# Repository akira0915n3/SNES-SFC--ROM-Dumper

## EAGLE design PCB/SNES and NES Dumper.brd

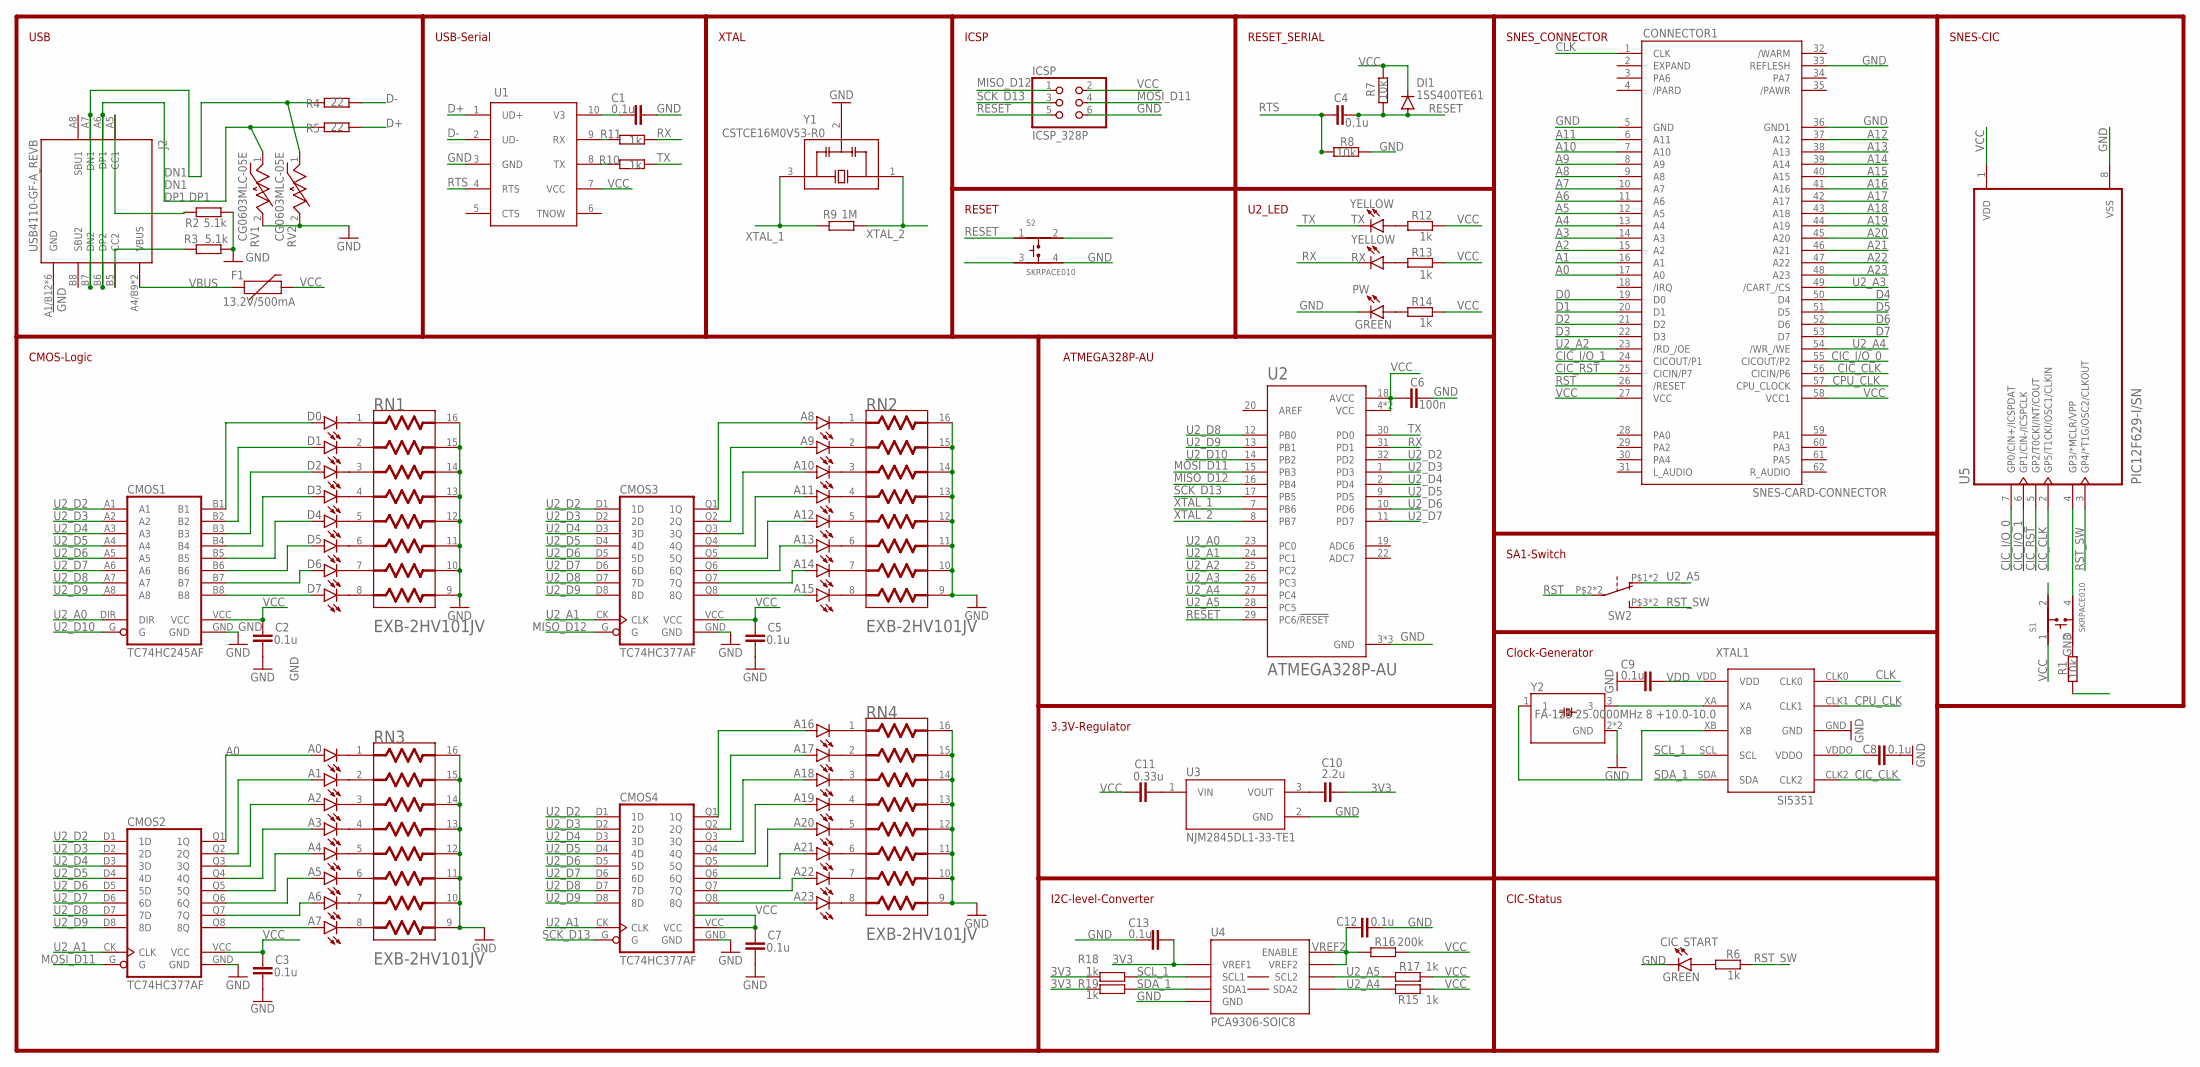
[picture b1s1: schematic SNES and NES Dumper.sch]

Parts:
A0, A1, A2, A3, A4, A5, A6, A7, A8, A9, A10, A11, A12, A13, A14, A15, A16, A17, A18, A19, A20, A21, A22, A23: YELLOW; SML0805
C1, C2, C3, C4, C5, C7, C8, C9, C12, C13: 0.1u; C0603
C6: 100n; C0603
C10: 2.2u; C0603
C11: 0.33u; C0603
CIC_START: GREEN; SML0805
CMOS1: TC74HC245AF; SO20W
CMOS2, CMOS3, CMOS4: TC74HC377AF; SO20W
CONNECTOR1: SNES-CARD-CONNECTOR; CON
D0, D1, D2, D3, D4, D5, D6, D7: YELLOW; SML0805
DI1: 1SS400TE61; SOD523
F1: 13.2V/500mA; 1206
ICSP: ICSP_328P; 2X03
J2: USB4110-GF-A_REVB; GCT_USB4110-GF-A_REVB
PW: GREEN; SML0805
R1, R7, R8: 10k; R0603
R2, R3: 5.1k; R0603
R4, R5: 22; R0603
R6, R10, R11, R12, R13, R14, R15, R17, R18, R19: 1k; R0603
R9: 1M; R0603
R16: 200k; R0603
RN1, RN2, RN3, RN4: PANASONIC_EXB-2HV101JVPANASONIC_EXB-2HV101JV_0_0; PANASONIC_EXB-2HV101JV_0
RV1, RV2: CG0603MLC-05E; VARC1608X56N
RX: YELLOW; SML0805
S1, S2: SKRPACE010; SW_SKRPACE010
SW2: ALPS_SSSS213202
TX: YELLOW; SML0805
U1: CH340E; MSOP10
U2: ATMEGA328P-AU; QFP80P900X900X120-32N
U3: NJM2845DL1-33-TE1; DPAK228P968X238-4N
U4: PCA9306-SOIC8; SOIC-8
U5: PIC12F629-I/SN; SOIC127P600X175-8N
XTAL1: SI5351; SI5351A-B-GTR
Y1: CSTCE16M0V53-R0; OSC_CSTCE16M0V53-R0
Y2: FA-128 25.0000MHz 8 +10.0-10.0; OSCSC320X250X100N

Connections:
3V3: C10.2, C13.2, R18.2, R19.2, U4.1 (VREF1)
A0: A0.A, CMOS2.Q1 (1Q), CONNECTOR1.17 (A0)
A1: A1.A, CMOS2.Q2 (2Q), CONNECTOR1.16 (A1)
A2: A2.A, CMOS2.Q3 (3Q), CONNECTOR1.15 (A2)
A3: A3.A, CMOS2.Q4 (4Q), CONNECTOR1.14 (A3)
A4: A4.A, CMOS2.Q5 (5Q), CONNECTOR1.13 (A4)
A5: A5.A, CMOS2.Q6 (6Q), CONNECTOR1.12 (A5)
A6: A6.A, CMOS2.Q7 (7Q), CONNECTOR1.11 (A6)
A7: A7.A, CMOS2.Q8 (8Q), CONNECTOR1.10 (A7)
A8: A8.A, CMOS3.Q1 (1Q), CONNECTOR1.9 (A8)
A9: A9.A, CMOS3.Q2 (2Q), CONNECTOR1.8 (A9)
A10: A10.A, CMOS3.Q3 (3Q), CONNECTOR1.7 (A10)
A11: A11.A, CMOS3.Q4 (4Q), CONNECTOR1.6 (A11)
A12: A12.A, CMOS3.Q5 (5Q), CONNECTOR1.37 (A12)
A13: A13.A, CMOS3.Q6 (6Q), CONNECTOR1.38 (A13)
A14: A14.A, CMOS3.Q7 (7Q), CONNECTOR1.39 (A14)
A15: A15.A, CMOS3.Q8 (8Q), CONNECTOR1.40 (A15)
A16: A16.A, CMOS4.Q1 (1Q), CONNECTOR1.41 (A16)
A17: A17.A, CMOS4.Q2 (2Q), CONNECTOR1.42 (A17)
A18: A18.A, CMOS4.Q3 (3Q), CONNECTOR1.43 (A18)
A19: A19.A, CMOS4.Q4 (4Q), CONNECTOR1.44 (A19)
A20: A20.A, CMOS4.Q5 (5Q), CONNECTOR1.45 (A20)
A21: A21.A, CMOS4.Q6 (6Q), CONNECTOR1.46 (A21)
A22: A22.A, CMOS4.Q7 (7Q), CONNECTOR1.47 (A22)
A23: A23.A, CMOS4.Q8 (8Q), CONNECTOR1.48 (A23)
CIC_CLK: CONNECTOR1.56 (CICIN/P6), U5.2 (GP5/T1CKI/OSC1/CLKIN), XTAL1.CLK2
CIC_I/O_0: CONNECTOR1.55 (CICOUT/P2), U5.7 (GP0/CIN+/ICSPDAT)
CIC_I/O_1: CONNECTOR1.24 (CICOUT/P1), U5.6 (GP1/CIN-/ICSPCLK)
CIC_RST: CONNECTOR1.25 (CICIN/P7), U5.5 (GP2/T0CKI/INT/COUT)
CLK: CONNECTOR1.1 (CLK), XTAL1.CLK0
CPU_CLK: CONNECTOR1.57 (CPU_CLOCK), XTAL1.CLK1
D0: CMOS1.B1, CONNECTOR1.19 (D0), D0.A
D1: CMOS1.B2, CONNECTOR1.20 (D1), D1.A
D2: CMOS1.B3, CONNECTOR1.21 (D2), D2.A
D3: CMOS1.B4, CONNECTOR1.22 (D3), D3.A
D4: CMOS1.B5, CONNECTOR1.50 (D4), D4.A
D5: CMOS1.B6, CONNECTOR1.51 (D5), D5.A
D6: CMOS1.B7, CONNECTOR1.52 (D6), D6.A
D7: CMOS1.B8, CONNECTOR1.53 (D7), D7.A
D+: R5.2, U1.1 (UD+)
D-: R4.2, U1.2 (UD-)
DN1: J2.A7 (DN1), J2.B7 (DN2), R4.1, RV2.1
DP1: J2.A6 (DP1), J2.B6 (DP2), R5.1, RV1.1
GND: C1.2, C2.1, C3.1, C5.1, C6.2, C7.1, C8.1, C9.1, C12.1, C13.1, CIC_START.C, CMOS1.GND, CMOS2.GND, CMOS3.GND, CMOS4.GND, CONNECTOR1.5 (GND), CONNECTOR1.33 (REFLESH), CONNECTOR1.36 (GND1), ICSP.6, J2.A1/B12 (GND), J2.B1/A12 (GND), J2.S1 (GND), J2.S2 (GND), J2.S3 (GND), J2.S4 (GND), PW.C, R1.2, R2.2, R3.2, R8.1, RN1.9, RN1.10, RN1.11, RN1.12, RN1.13, RN1.14, RN1.15, RN1.16, RN2.9, RN2.10, RN2.11, RN2.12, RN2.13, RN2.14, RN2.15, RN2.16, RN3.9, RN3.10, RN3.11, RN3.12, RN3.13, RN3.14, RN3.15, RN3.16, RN4.9, RN4.10, RN4.11, RN4.12, RN4.13, RN4.14, RN4.15, RN4.16, RV1.2, RV2.2, S2.3, S2.4, U1.3 (GND), U2.3 (GND), U2.5 (GND), U2.21 (GND), U3.2 (GND), U4.4 (GND), U5.8 (VSS), XTAL1.GND, Y1.2 (GND), Y2.2 (GND), Y2.4 (GND)
MISO_D12: CMOS3.G, ICSP.1, U2.16 (PB4)
MOSI_D11: CMOS2.G, ICSP.4, U2.15 (PB3)
unnamed: C1.1, U1.10 (V3)
unnamed: R11.2, U1.9 (RX)
unnamed: R10.2, U1.8 (TX)
unnamed: D0.C, RN1.1
unnamed: PW.A, R14.2
unnamed: D1.C, RN1.2
unnamed: D2.C, RN1.3
unnamed: D3.C, RN1.4
unnamed: D4.C, RN1.5
unnamed: D5.C, RN1.6
unnamed: D6.C, RN1.7
unnamed: D7.C, RN1.8
unnamed: A8.C, RN2.1
unnamed: A9.C, RN2.2
unnamed: A10.C, RN2.3
unnamed: A11.C, RN2.4
unnamed: A12.C, RN2.5
unnamed: A13.C, RN2.6
unnamed: A14.C, RN2.7
unnamed: A15.C, RN2.8
unnamed: R12.2, TX.A
unnamed: J2.B5 (CC2), R3.1
unnamed: J2.A5 (CC1), R2.1
unnamed: A0.C, RN3.1
unnamed: A1.C, RN3.2
unnamed: A2.C, RN3.3
unnamed: A3.C, RN3.4
unnamed: A4.C, RN3.5
unnamed: A5.C, RN3.6
unnamed: A6.C, RN3.7
unnamed: A7.C, RN3.8
unnamed: A16.C, RN4.1
unnamed: A17.C, RN4.2
unnamed: A18.C, RN4.3
unnamed: A19.C, RN4.4
unnamed: A20.C, RN4.5
unnamed: A21.C, RN4.6
unnamed: A22.C, RN4.7
unnamed: A23.C, RN4.8
unnamed: XTAL1.XA, Y2.3
unnamed: XTAL1.XB, Y2.1
unnamed: R13.2, RX.A
unnamed: C10.1, U3.3 (VOUT)
unnamed: C11.2, U3.1 (VIN)
unnamed: CIC_START.A, R6.2
unnamed: S1.4, U5.4 (GP3/*MCLR/VPP)
unnamed: R1.1, S1.3
RESET: C4.2, DI1.A, ICSP.5, R7.1, S2.1, S2.2, U2.29 (PC6/!RESET)
RST: CONNECTOR1.26 (/RESET), SW2.P$2 (2), SW2.P$5 (2)
RST_SW: R6.1, SW2.P$3 (3), SW2.P$4 (3), U5.3 (GP4/*T1G/OSC2/CLKOUT)
RTS: C4.1, R8.2, U1.4 (RTS)
RX: R11.1, RX.C, U2.31 (PD1)
SCK_D13: CMOS4.G, ICSP.3, U2.17 (PB5)
SCL_1: R18.1, U4.2 (SCL1), XTAL1.SCL
SDA_1: R19.1, U4.3 (SDA1), XTAL1.SDA
TX: R10.1, TX.C, U2.30 (PD0)
U2_A0: CMOS1.DIR, U2.23 (PC0)
U2_A1: CMOS2.CK (CLK), CMOS3.CK (CLK), CMOS4.CK (CLK), U2.24 (PC1)
U2_A2: CONNECTOR1.23 (/RD_/OE), U2.25 (PC2)
U2_A3: CONNECTOR1.49 (/CART_/CS), U2.26 (PC3)
U2_A4: CONNECTOR1.54 (/WR_/WE), R15.2, U2.27 (PC4), U4.5 (SDA2)
U2_A5: R17.2, SW2.P$1 (1), SW2.P$6 (1), U2.28 (PC5), U4.6 (SCL2)
U2_D2: CMOS1.A1, CMOS2.D1 (1D), CMOS3.D1 (1D), CMOS4.D1 (1D), U2.32 (PD2)
U2_D3: CMOS1.A2, CMOS2.D2 (2D), CMOS3.D2 (2D), CMOS4.D2 (2D), U2.1 (PD3)
U2_D4: CMOS1.A3, CMOS2.D3 (3D), CMOS3.D3 (3D), CMOS4.D3 (3D), U2.2 (PD4)
U2_D5: CMOS1.A4, CMOS2.D4 (4D), CMOS3.D4 (4D), CMOS4.D4 (4D), U2.9 (PD5)
U2_D6: CMOS1.A5, CMOS2.D5 (5D), CMOS3.D5 (5D), CMOS4.D5 (5D), U2.10 (PD6)
U2_D7: CMOS1.A6, CMOS2.D6 (6D), CMOS3.D6 (6D), CMOS4.D6 (6D), U2.11 (PD7)
U2_D8: CMOS1.A7, CMOS2.D7 (7D), CMOS3.D7 (7D), CMOS4.D7 (7D), U2.12 (PB0)
U2_D9: CMOS1.A8, CMOS2.D8 (8D), CMOS3.D8 (8D), CMOS4.D8 (8D), U2.13 (PB1)
U2_D10: CMOS1.G, U2.14 (PB2)
VBUS: F1.1, J2.A4/B9 (VBUS), J2.B4/A9 (VBUS)
VCC: C2.2, C3.2, C5.2, C6.1, C7.2, C11.1, CMOS1.VCC, CMOS2.VCC, CMOS3.VCC, CMOS4.VCC, CONNECTOR1.27 (VCC), CONNECTOR1.58 (VCC1), DI1.C, F1.2, ICSP.2, R7.2, R12.1, R13.1, R14.1, R15.1, R16.1, R17.1, S1.1, S1.2, U1.7 (VCC), U2.4 (VCC), U2.6 (VCC), U2.18 (AVCC), U5.1 (VDD)
VDD: C9.2, XTAL1.VDD
VDDO: C8.2, XTAL1.VDDO
VREF2: C12.2, R16.2, U4.7 (VREF2), U4.8 (ENABLE)
XTAL_1: R9.1, U2.7 (PB6), Y1.3 (OUT)
XTAL_2: R9.2, U2.8 (PB7), Y1.1 (IN)

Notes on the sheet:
RESET
USB
RESET_SERIAL
ICSP
XTAL
USB-Serial
U2_LED
ATMEGA328P-AU
SNES_CONNECTOR
CMOS-Logic
3.3V-Regulator
I2C-level-Converter
SA1-Switch
CIC-Status
SNES-CIC
Clock-Generator

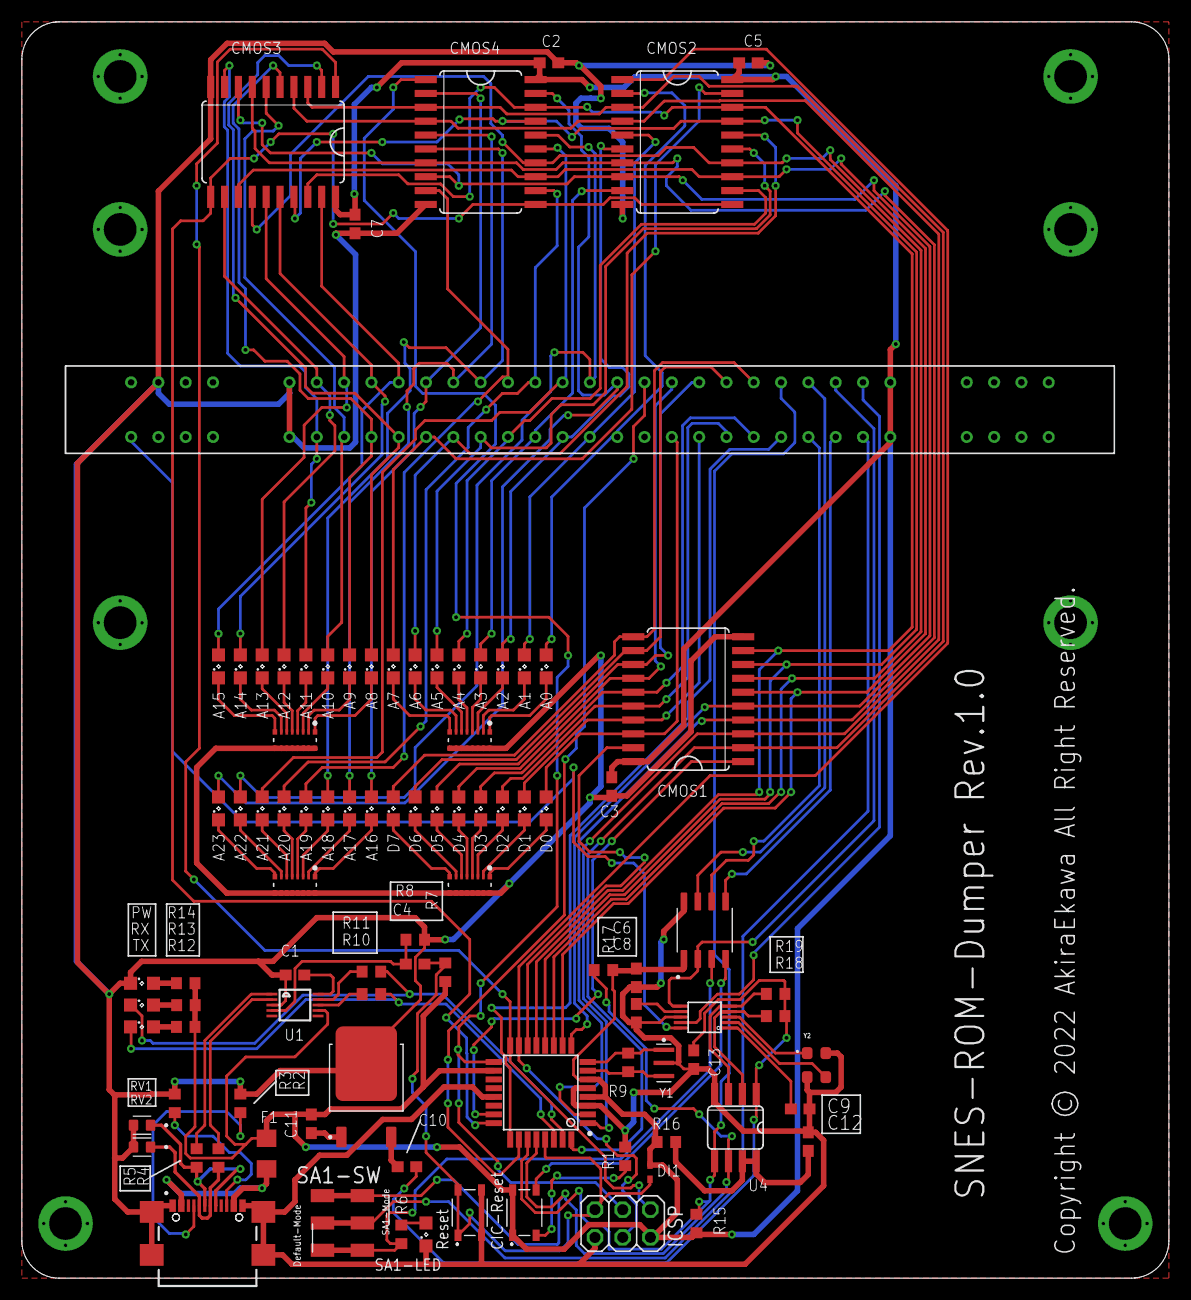
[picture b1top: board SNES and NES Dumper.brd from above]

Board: 2 copper layers, 105.0 x 115.0 mm, 94 parts (0 on the bottom side), 124 nets.

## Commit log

2022-07-31 Create PCB

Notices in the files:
PCB/SNES and NES Dumper.brd:
Copyright © 2022 AkiraEkawa All Right Reserved.
parts and their libraries:
SparkFun-Fuses: Licensing: Creative Commons ShareAlike 4.0 International - https://creativecommons.org/licenses/by-sa/4.0
